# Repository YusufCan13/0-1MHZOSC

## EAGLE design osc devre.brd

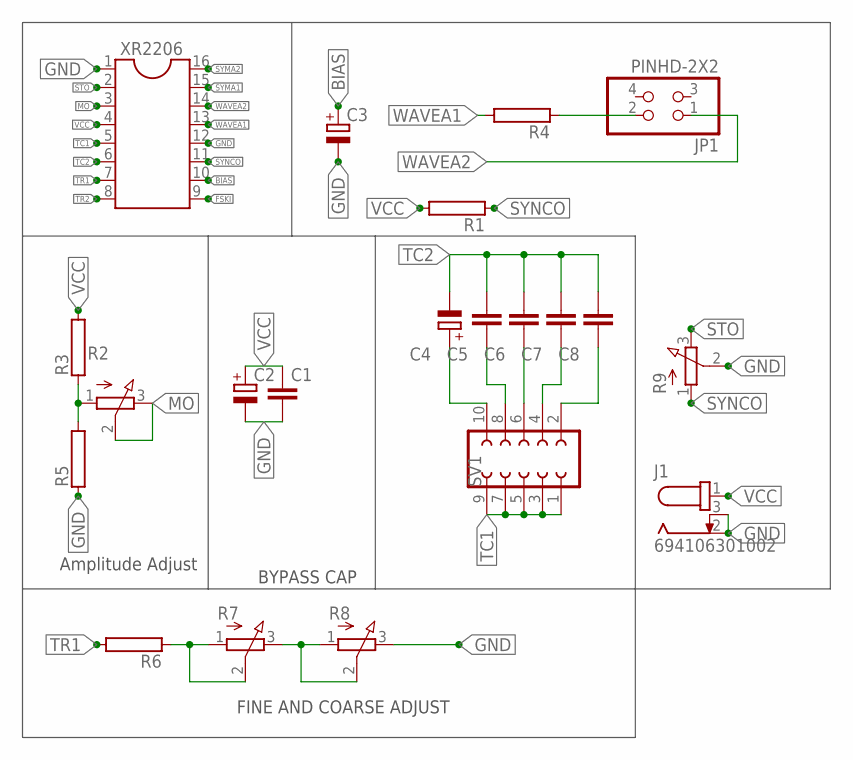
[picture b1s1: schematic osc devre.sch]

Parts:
C1, C5, C6, C7, C8: C5/3; C5B3
C2, C3: C-POL_RADIAL-11MM-DIA; CAPPRD508W65D1000H1100B
C4: CPOL-EUE2.5-5; E2,5-5
J1: 694106301002
JP1: PINHD-2X2; 2X02
R1, R3, R4, R5, R6: RCA0001; CA0001
R2, R7, R8, R9: 3RP/1610N
SV1: FE05-2
XR2206: DIL16

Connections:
BIAS: C3.1 (+), XR2206.10
FSKI: XR2206.9
GND: C1.2, C2.2 (-), C3.2 (-), J1.2, J1.3, R5.1, R8.3 (E), R9.2 (S), XR2206.1, XR2206.12
MO: R2.2 (S), R2.3 (E), XR2206.3
unnamed: R6.1, R7.1 (A), R7.2 (S)
unnamed: JP1.2, R4.1
unnamed: R7.3 (E), R8.1 (A), R8.2 (S)
unnamed: C8.1, SV1.2
unnamed: R2.1 (A), R3.1, R5.2
unnamed: C7.1, SV1.4
unnamed: C6.1, SV1.6
unnamed: C5.1, SV1.8
unnamed: C4.+, SV1.10
STO: R9.3 (E), XR2206.2
SYMA1: XR2206.15
SYMA2: XR2206.16
SYNCO: R1.1, R9.1 (A), XR2206.11
TC1: SV1.1, SV1.3, SV1.5, SV1.7, SV1.9, XR2206.5
TC2: C4.-, C5.2, C6.2, C7.2, C8.2, XR2206.6
TR1: R6.2, XR2206.7
TR2: XR2206.8
VCC: C1.1, C2.1 (+), J1.1, R1.2, R3.2, XR2206.4
WAVEA1: R4.2, XR2206.13
WAVEA2: JP1.1, XR2206.14

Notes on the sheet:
Amplitude Adjust
BYPASS CAP
FINE AND COARSE ADJUST

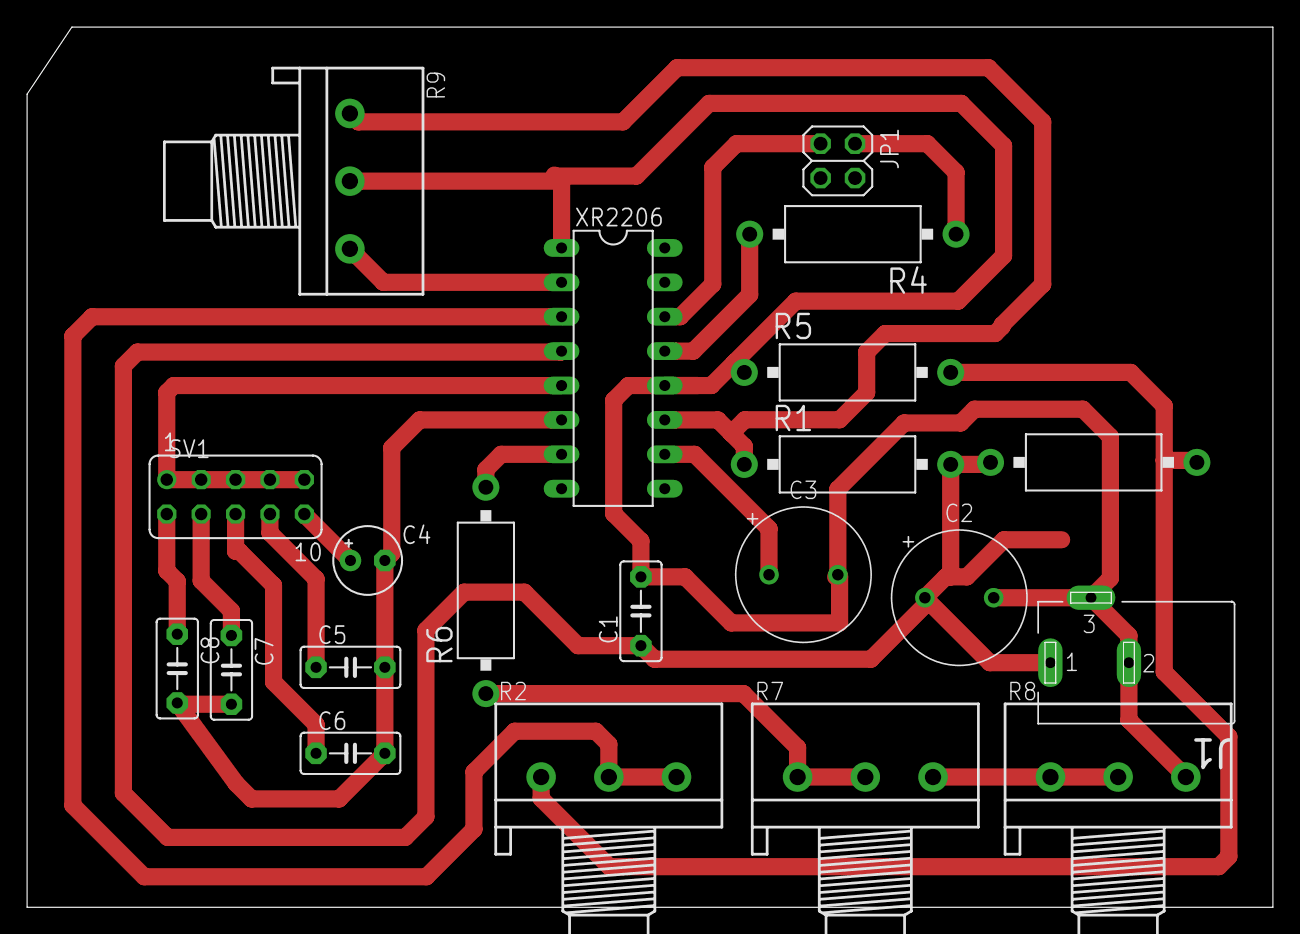
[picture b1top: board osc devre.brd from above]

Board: 2 copper layers, 92.0 x 65.0 mm, 21 parts (0 on the bottom side), 20 nets.
